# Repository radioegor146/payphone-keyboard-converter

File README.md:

# payphone-keyboard-converter

Simple converter from 4x4 matrix payphone keyboard to 6x7 custom keyboard of LevelOne VOI-7000 SIP phone based on EPM7128STC100-15 CPLD from Altera

- `hardware/` - KiCad project for the board itself
- `fpga/` - Quartus II project for CPLD

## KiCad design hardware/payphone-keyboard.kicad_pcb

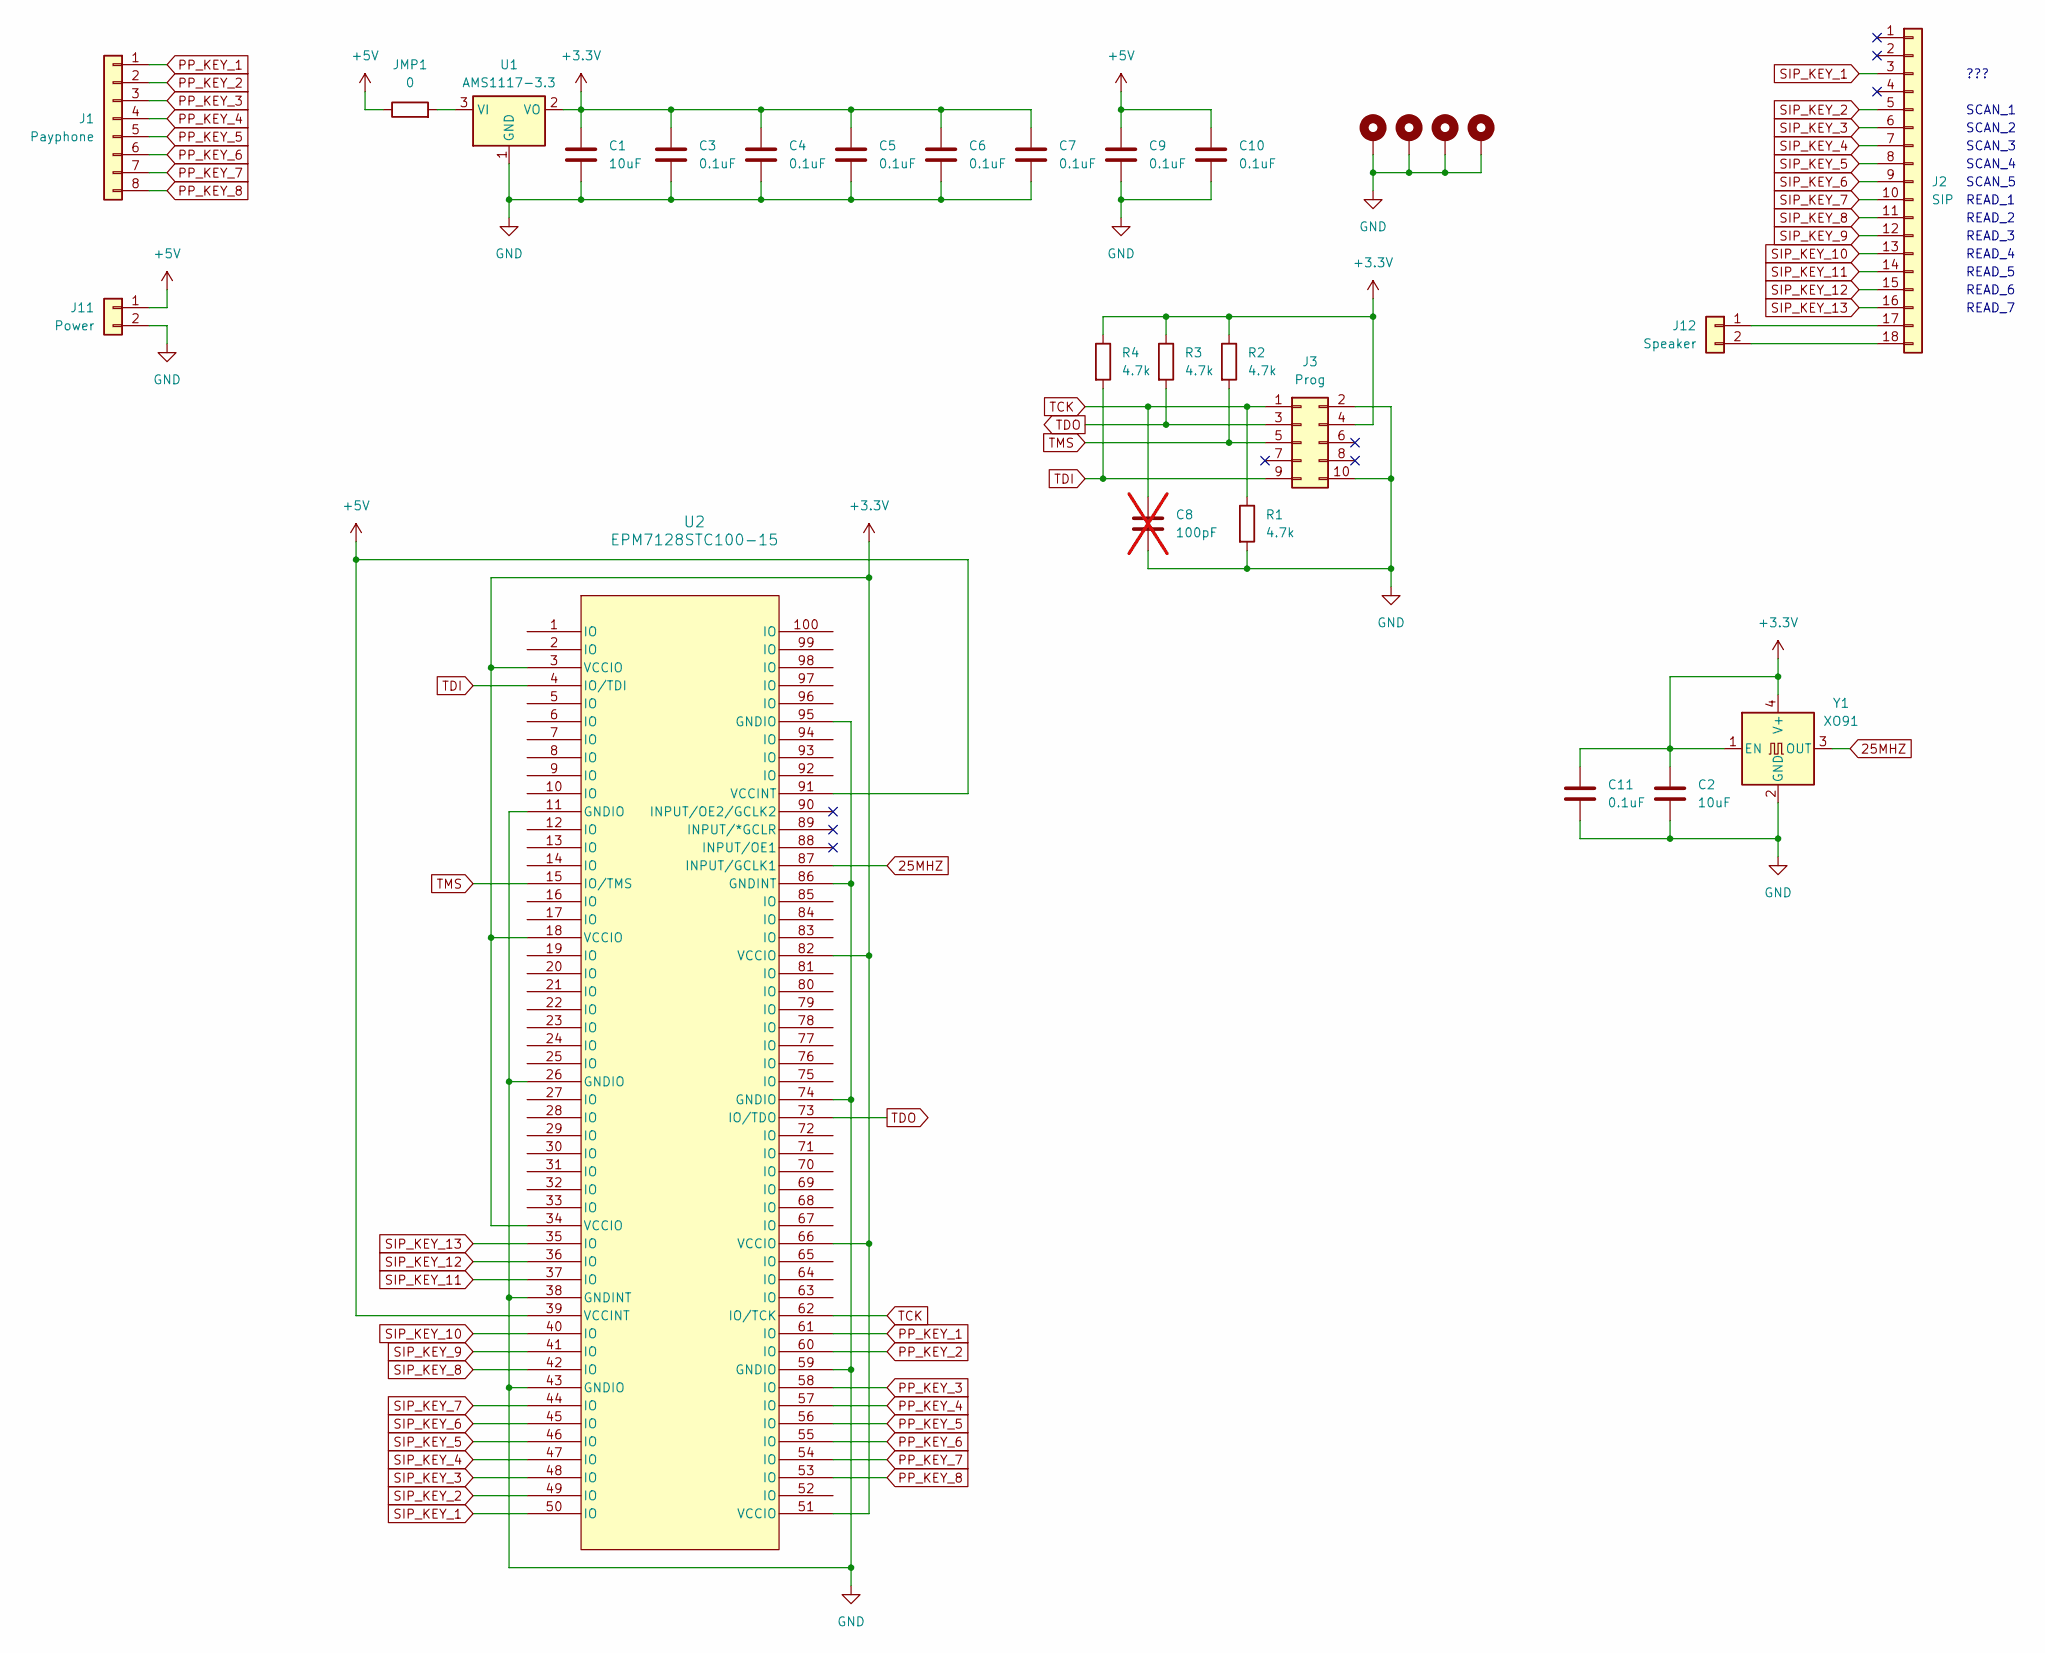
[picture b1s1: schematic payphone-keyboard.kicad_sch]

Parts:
C1, C2: 10uF; C_0805_2012Metric
C3, C4, C5, C6, C7, C9, C10, C11: 0.1uF; C_0805_2012Metric
C8: 100pF; C_0805_2012Metric; not fitted
H1, H2, H3, H4: MountingHole_Pad; MountingHole_3.2mm_M3_DIN965_Pad_TopOnly
J1: Payphone; JST_XH_B8B-XH-A_1x08_P2.50mm_Vertical
J2: SIP; PinHeader_1x18_P2.00mm_Vertical
J3: Prog; IDC-Header_2x05_P2.54mm_Vertical
J11: Power; JST_XH_B2B-XH-A_1x02_P2.50mm_Vertical
J12: Speaker; JST_XH_B2B-XH-A_1x02_P2.50mm_Vertical
JMP1: 0; R_1206_3216Metric
R1, R2, R3, R4: 4.7k; R_0805_2012Metric
U1: AMS1117-3.3; SOT-223-3_TabPin2
U2: EPM7128STC100-15; TQFP-100_14x14mm_P0.5mm
Y1: XO91; Oscillator_SMD_EuroQuartz_XO91-4Pin_7.0x5.0mm_HandSoldering

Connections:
25MHZ: U2.87 (INPUT/GCLK1), Y1.3 (OUT)
+3.3V: C1.1, C2.1, C3.1, C4.1, C5.1, C6.1, C7.1, C11.1, J3.4, R2.1, R3.1, R4.1, U1.2 (VO), U2.3 (VCCIO), U2.18 (VCCIO), U2.34 (VCCIO), U2.51 (VCCIO), U2.66 (VCCIO), U2.82 (VCCIO), Y1.1 (EN), Y1.4 (V+)
+5V: C9.1, C10.1, J11.1, JMP1.1, U2.39 (VCCINT), U2.91 (VCCINT)
GND: C1.2, C2.2, C3.2, C4.2, C5.2, C6.2, C7.2, C8.2, C9.2, C10.2, C11.2, H1.1, H2.1, H3.1, H4.1, J3.2, J3.10, J11.2, R1.2, U1.1 (GND), U2.11 (GNDIO), U2.26 (GNDIO), U2.38 (GNDINT), U2.43 (GNDIO), U2.59 (GNDIO), U2.74 (GNDIO), U2.86 (GNDINT), U2.95 (GNDIO), Y1.2 (GND)
unnamed: J2.17, J12.1
unnamed: J2.18, J12.2
unnamed: JMP1.2, U1.3 (VI)
PP_KEY_1: J1.1, U2.61 (IO)
PP_KEY_2: J1.2, U2.60 (IO)
PP_KEY_3: J1.3, U2.58 (IO)
PP_KEY_4: J1.4, U2.57 (IO)
PP_KEY_5: J1.5, U2.56 (IO)
PP_KEY_6: J1.6, U2.55 (IO)
PP_KEY_7: J1.7, U2.54 (IO)
PP_KEY_8: J1.8, U2.53 (IO)
SIP_KEY_1: J2.3, U2.50 (IO)
SIP_KEY_2: J2.5, U2.49 (IO)
SIP_KEY_3: J2.6, U2.48 (IO)
SIP_KEY_4: J2.7, U2.47 (IO)
SIP_KEY_5: J2.8, U2.46 (IO)
SIP_KEY_6: J2.9, U2.45 (IO)
SIP_KEY_7: J2.10, U2.44 (IO)
SIP_KEY_8: J2.11, U2.42 (IO)
SIP_KEY_9: J2.12, U2.41 (IO)
SIP_KEY_10: J2.13, U2.40 (IO)
SIP_KEY_11: J2.14, U2.37 (IO)
SIP_KEY_12: J2.15, U2.36 (IO)
SIP_KEY_13: J2.16, U2.35 (IO)
TCK: C8.1, J3.1, R1.1, U2.62 (IO/TCK)
TDI: J3.9, R4.2, U2.4 (IO/TDI)
TDO: J3.3, R3.2, U2.73 (IO/TDO)
TMS: J3.5, R2.2, U2.15 (IO/TMS)

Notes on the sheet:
SCAN_2
SCAN_3
READ_2
READ_3
READ_6
SCAN_4
READ_5
SCAN_1
READ_4
SCAN_5
READ_7
READ_1
???

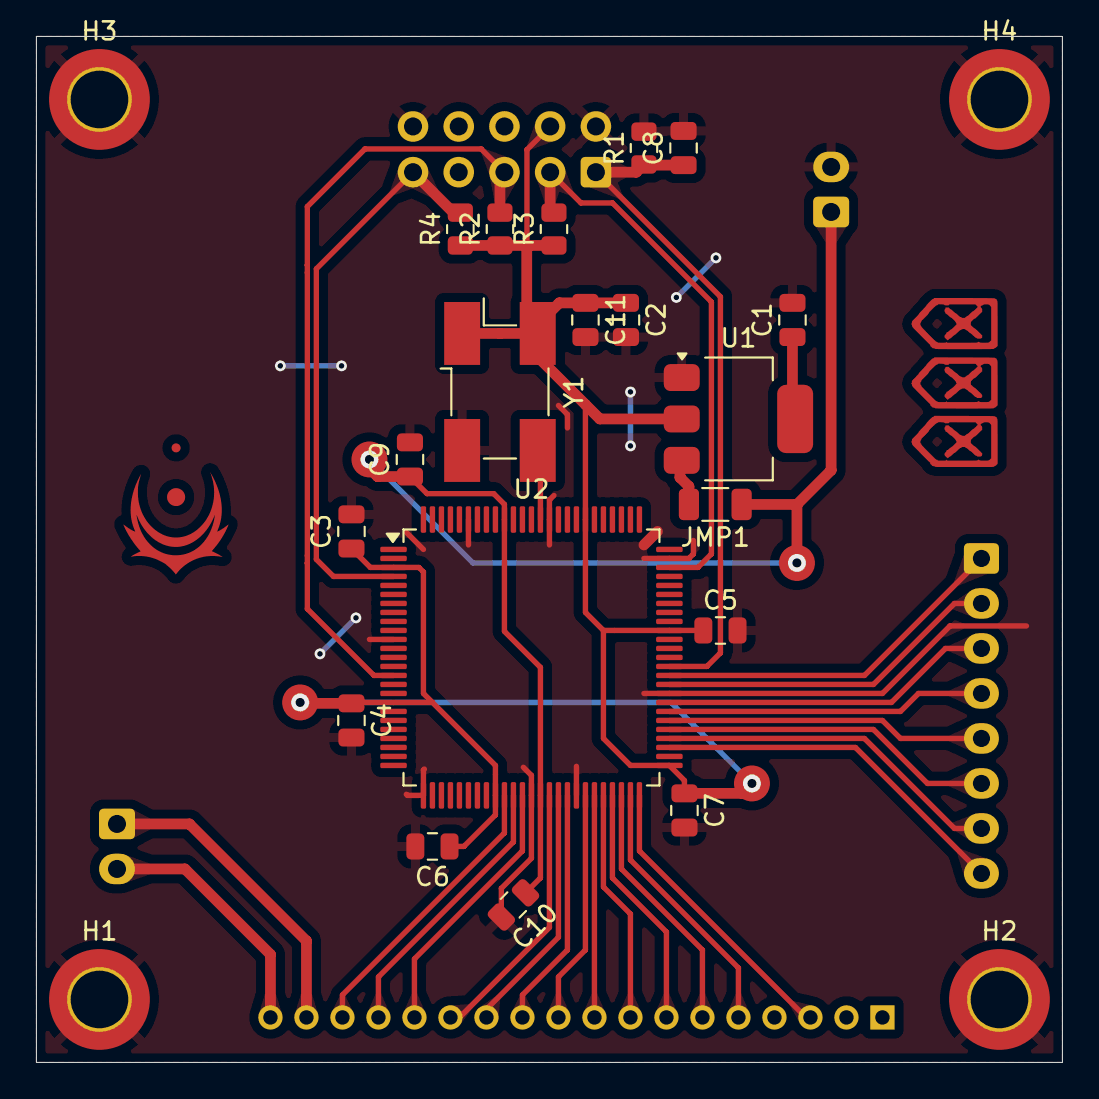
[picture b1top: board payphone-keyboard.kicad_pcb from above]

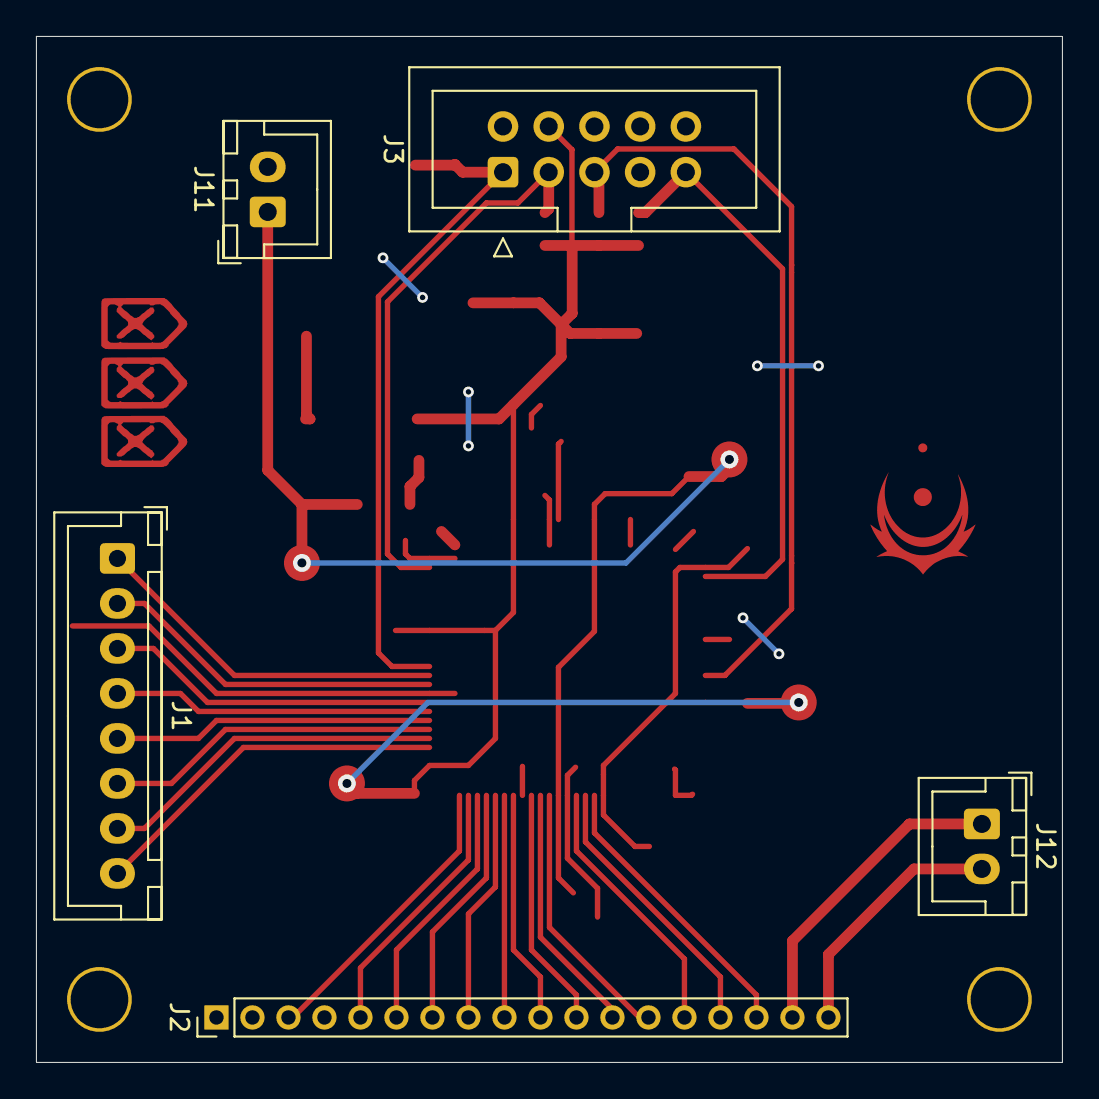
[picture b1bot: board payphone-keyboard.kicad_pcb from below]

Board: 2 copper layers, 57.0 x 57.0 mm, 28 parts (5 on the bottom side), 32 nets.

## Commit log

2025-04-01 main commit
2025-04-01 change readme
2025-04-01 add pdf to schematic
